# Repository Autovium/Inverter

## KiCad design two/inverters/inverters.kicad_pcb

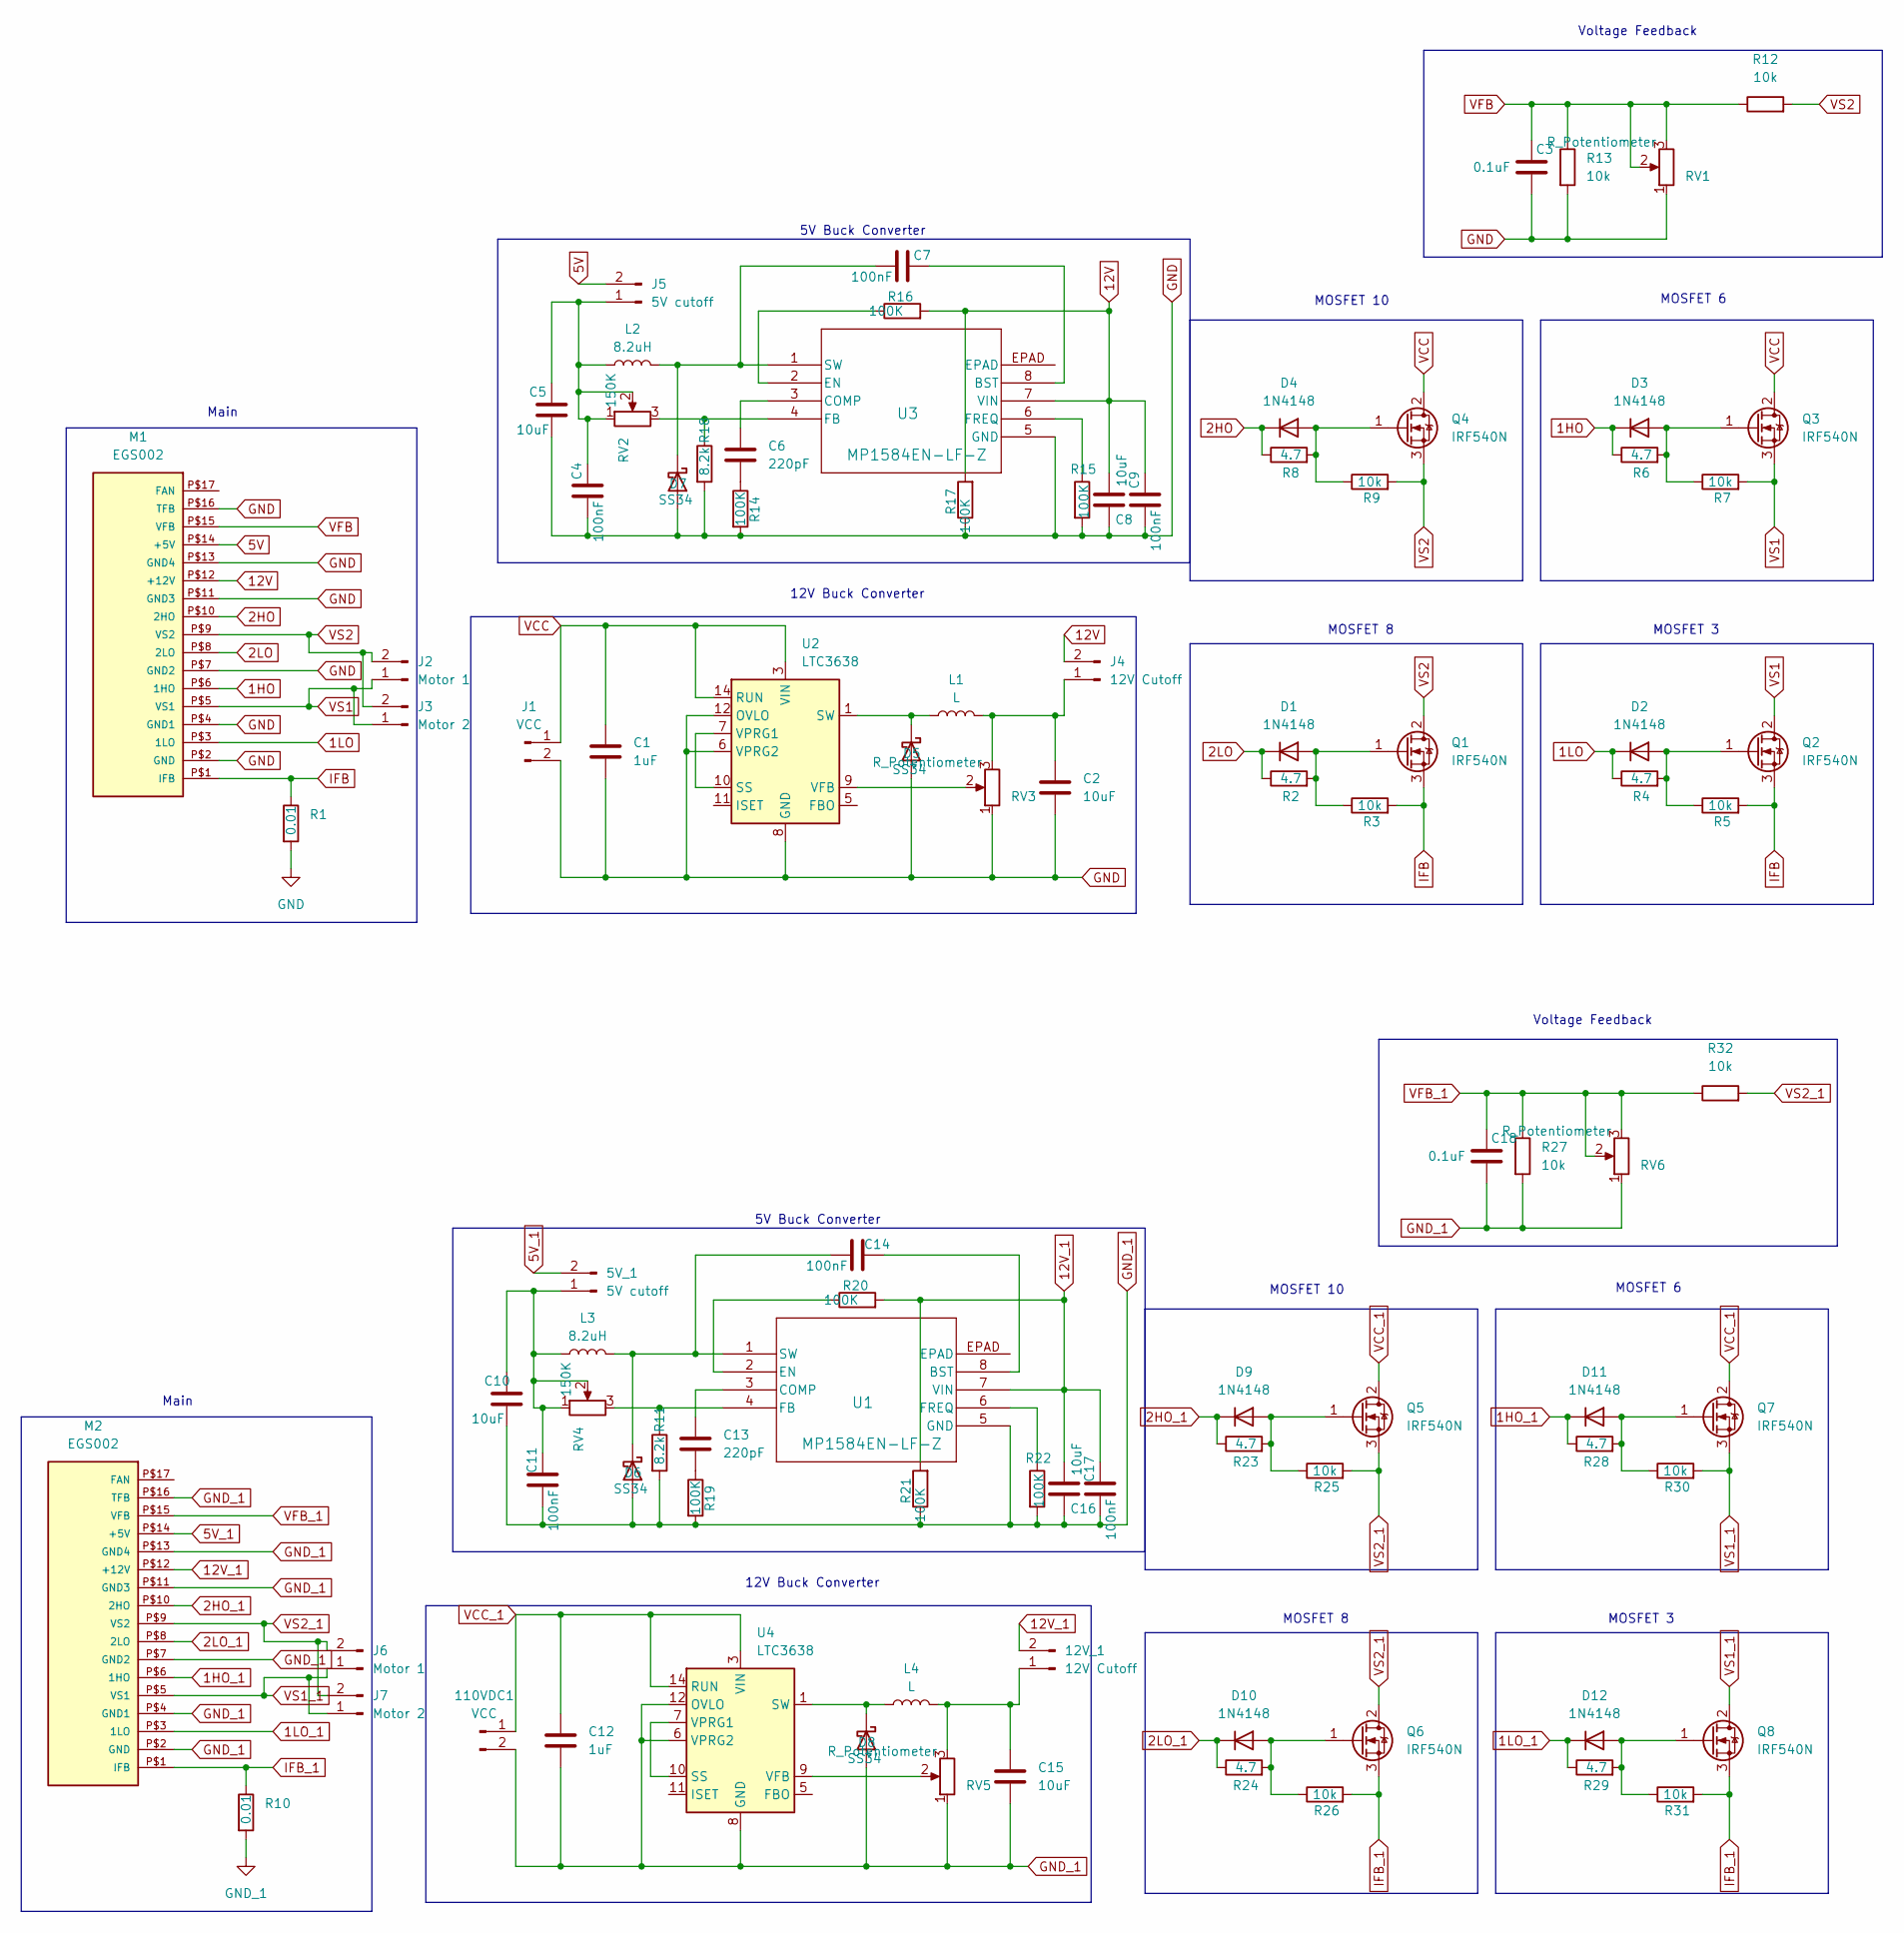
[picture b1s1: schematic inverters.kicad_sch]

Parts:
5V_1: 5V cutoff; SolderJumper-2_P1.3mm_Open_Pad1.0x1.5mm
12V_1: 12V Cutoff; SolderJumper-2_P1.3mm_Open_Pad1.0x1.5mm
110VDC1: VCC; PinHeader_1x02_P2.54mm_Vertical
C1: 1uF; C_Disc_D3.0mm_W1.6mm_P2.50mm
C2: 10uF; C_Disc_D3.0mm_W1.6mm_P2.50mm
C3, C18: 0.1uF; C_Disc_D3.0mm_W1.6mm_P2.50mm
C4, C7, C9, C11, C14, C17: 100nF; C_0201_0603Metric_Pad0.64x0.40mm_HandSolder
C5, C8, C10, C16: 10uF; C_1206_3216Metric_Pad1.33x1.80mm_HandSolder
C6, C13: 220pF; C_0201_0603Metric_Pad0.64x0.40mm_HandSolder
C12: 1uF; CP_Radial_D4.0mm_P2.00mm
C15: 10uF; CP_Radial_D4.0mm_P2.00mm
D1, D2, D3, D4, D9, D10, D11, D12: 1N4148; Nexperia_CFP3_SOD-123W
D5, D6, D7, D8: SS34; D_SMA_Handsoldering
J1: VCC; PinHeader_1x02_P2.54mm_Vertical
J2, J6: Motor 1; PinHeader_1x02_P2.54mm_Vertical
J3, J7: Motor 2; PinHeader_1x02_P2.54mm_Vertical
J4: 12V Cutoff; SolderJumper-2_P1.3mm_Open_Pad1.0x1.5mm
J5: 5V cutoff; PinHeader_1x02_P1.00mm_Vertical_SMD_Pin1Left
L1, L4: L; L_Radial_D6.0mm_P4.00mm
L2, L3: 8.2uH; L_Bourns_SRP6060FA
M1, M2: EGS002
Q1, Q2, Q3, Q4, Q5, Q6, Q7, Q8: IRF540N; TO-220-3_Vertical
R1: 0.01; R_Axial_DIN0204_L3.6mm_D1.6mm_P5.08mm_Horizontal
R2, R4, R6, R8: 4.7; R_0805_2012Metric_Pad1.20x1.40mm_HandSolder
R3, R5, R7, R9, R12, R13: 10k; R_0805_2012Metric_Pad1.20x1.40mm_HandSolder
R10: 0.01; R_Axial_DIN0207_L6.3mm_D2.5mm_P7.62mm_Horizontal
R11, R18: 8.2k; R_0201_0603Metric_Pad0.64x0.40mm_HandSolder
R14, R15, R16, R17, R19, R20, R21, R22: 100K; R_0201_0603Metric_Pad0.64x0.40mm_HandSolder
R23, R24, R28, R29: 4.7; R_Axial_DIN0207_L6.3mm_D2.5mm_P7.62mm_Horizontal
R25, R26, R27, R30, R31, R32: 10k; R_Axial_DIN0207_L6.3mm_D2.5mm_P7.62mm_Horizontal
RV1, RV3, RV5, RV6: R_Potentiometer; Potentiometer_Bourns_3266Y_Vertical
RV2, RV4: 150K; Potentiometer_Bourns_TC33X_Vertical
U1, U3: MP1584EN-LF-Z; SOIC8E_MPS
U2, U4: LTC3638; Linear_MSOP-12-16-1EP_3x4mm_P0.5mm

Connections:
1HO: D3.1 (K), M1.P$6 (1HO), R6.1
1HO_1: D11.1 (K), M2.P$6 (1HO), R28.1
1LO: D2.1 (K), M1.P$3 (1LO), R4.1
1LO_1: D12.1 (K), M2.P$3 (1LO), R29.1
2HO: D4.1 (K), M1.P$10 (2HO), R8.1
2HO_1: D9.1 (K), M2.P$10 (2HO), R23.1
2LO: D1.1 (K), M1.P$8 (2LO), R2.1
2LO_1: D10.1 (K), M2.P$8 (2LO), R24.1
5V: J5.2, M1.P$14 (+5V)
5V_1: 5V_1.2, M2.P$14 (+5V)
12V: C8.1, C9.2, J4.2, M1.P$12 (+12V), R16.2, R17.2, U3.7 (VIN)
12V_1: 12V_1.2, C16.1, C17.2, M2.P$12 (+12V), R20.2, R21.2, U1.7 (VIN)
GND: C1.2, C2.2, C3.2, C4.1, C5.2, C8.2, C9.1, D5.2 (A), D7.2 (A), J1.2, M1.P$2 (GND), M1.P$4 (GND1), M1.P$7 (GND2), M1.P$11 (GND3), M1.P$13 (GND4), M1.P$16 (TFB), R1.2, R13.2, R14.2, R15.2, R17.1, R18.2, RV1.1, RV3.1, U2.6 (VPRG2), U2.8 (GND), U2.12 (OVLO), U2.16 (GND), U2.17 (GND), U3.5 (GND)
GND_1: 110VDC1.2, C10.2, C11.1, C12.2, C15.2, C16.2, C17.1, C18.2, D6.2 (A), D8.2 (A), M2.P$2 (GND), M2.P$4 (GND1), M2.P$7 (GND2), M2.P$11 (GND3), M2.P$13 (GND4), M2.P$16 (TFB), R10.2, R11.2, R19.2, R21.1, R22.2, R27.2, RV5.1, RV6.1, U1.5 (GND), U4.6 (VPRG2), U4.8 (GND), U4.12 (OVLO), U4.16 (GND), U4.17 (GND)
IFB: M1.P$1 (IFB), Q1.3 (S), Q2.3 (S), R1.1, R3.2, R5.2
IFB_1: M2.P$1 (IFB), Q6.3 (S), Q8.3 (S), R10.1, R26.2, R31.2
unnamed: 5V_1.1, C10.1, C11.2, L3.1, RV4.1, RV4.2
unnamed: 12V_1.1, C15.1, L4.2, RV5.3
unnamed: C6.2, R14.1
unnamed: C13.2, R19.1
unnamed: D1.2 (A), Q1.1 (G), R2.2, R3.1
unnamed: D2.2 (A), Q2.1 (G), R4.2, R5.1
unnamed: D3.2 (A), Q3.1 (G), R6.2, R7.1
unnamed: D4.2 (A), Q4.1 (G), R8.2, R9.1
unnamed: D5.1 (K), L1.1, U2.1 (SW)
unnamed: C14.1, D6.1 (K), L3.2, U1.1 (SW)
unnamed: C7.1, D7.1 (K), L2.2, U3.1 (SW)
unnamed: D8.1 (K), L4.1, U4.1 (SW)
unnamed: D9.2 (A), Q5.1 (G), R23.2, R25.1
unnamed: D10.2 (A), Q6.1 (G), R24.2, R26.1
unnamed: D11.2 (A), Q7.1 (G), R28.2, R30.1
unnamed: D12.2 (A), Q8.1 (G), R29.2, R31.1
unnamed: C2.1, J4.1, L1.2, RV3.3
unnamed: C4.2, C5.1, J5.1, L2.1, RV2.1, RV2.2
unnamed: C14.2, U1.8 (BST)
unnamed: C13.1, U1.3 (COMP)
unnamed: R20.1, U1.2 (EN)
unnamed: R11.1, RV4.3, U1.4 (FB)
unnamed: R22.1, U1.6 (FREQ)
unnamed: U2.7 (VPRG1), U2.10 (SS)
unnamed: RV3.2, U2.9 (VFB)
unnamed: C7.2, U3.8 (BST)
unnamed: C6.1, U3.3 (COMP)
unnamed: R16.1, U3.2 (EN)
unnamed: R18.1, RV2.3, U3.4 (FB)
unnamed: R15.1, U3.6 (FREQ)
unnamed: U4.7 (VPRG1), U4.10 (SS)
unnamed: RV5.2, U4.9 (VFB)
VCC: C1.1, J1.1, Q3.2 (D), Q4.2 (D), U2.3 (VIN), U2.14 (RUN)
VCC_1: 110VDC1.1, C12.1, Q5.2 (D), Q7.2 (D), U4.3 (VIN), U4.14 (RUN)
VFB: C3.1, M1.P$15 (VFB), R12.1, R13.1, RV1.2, RV1.3
VFB_1: C18.1, M2.P$15 (VFB), R27.1, R32.1, RV6.2, RV6.3
VS1: J2.1, J3.1, M1.P$5 (VS1), Q2.2 (D), Q3.3 (S), R7.2
VS1_1: J6.1, J7.1, M2.P$5 (VS1), Q7.3 (S), Q8.2 (D), R30.2
VS2: J2.2, J3.2, M1.P$9 (VS2), Q1.2 (D), Q4.3 (S), R9.2, R12.2
VS2_1: J6.2, J7.2, M2.P$9 (VS2), Q5.3 (S), Q6.2 (D), R25.2, R32.2

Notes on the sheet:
MOSFET 10
12V Buck Converter
Main
MOSFET 8
Voltage Feedback
5V Buck Converter
MOSFET 3
MOSFET 6

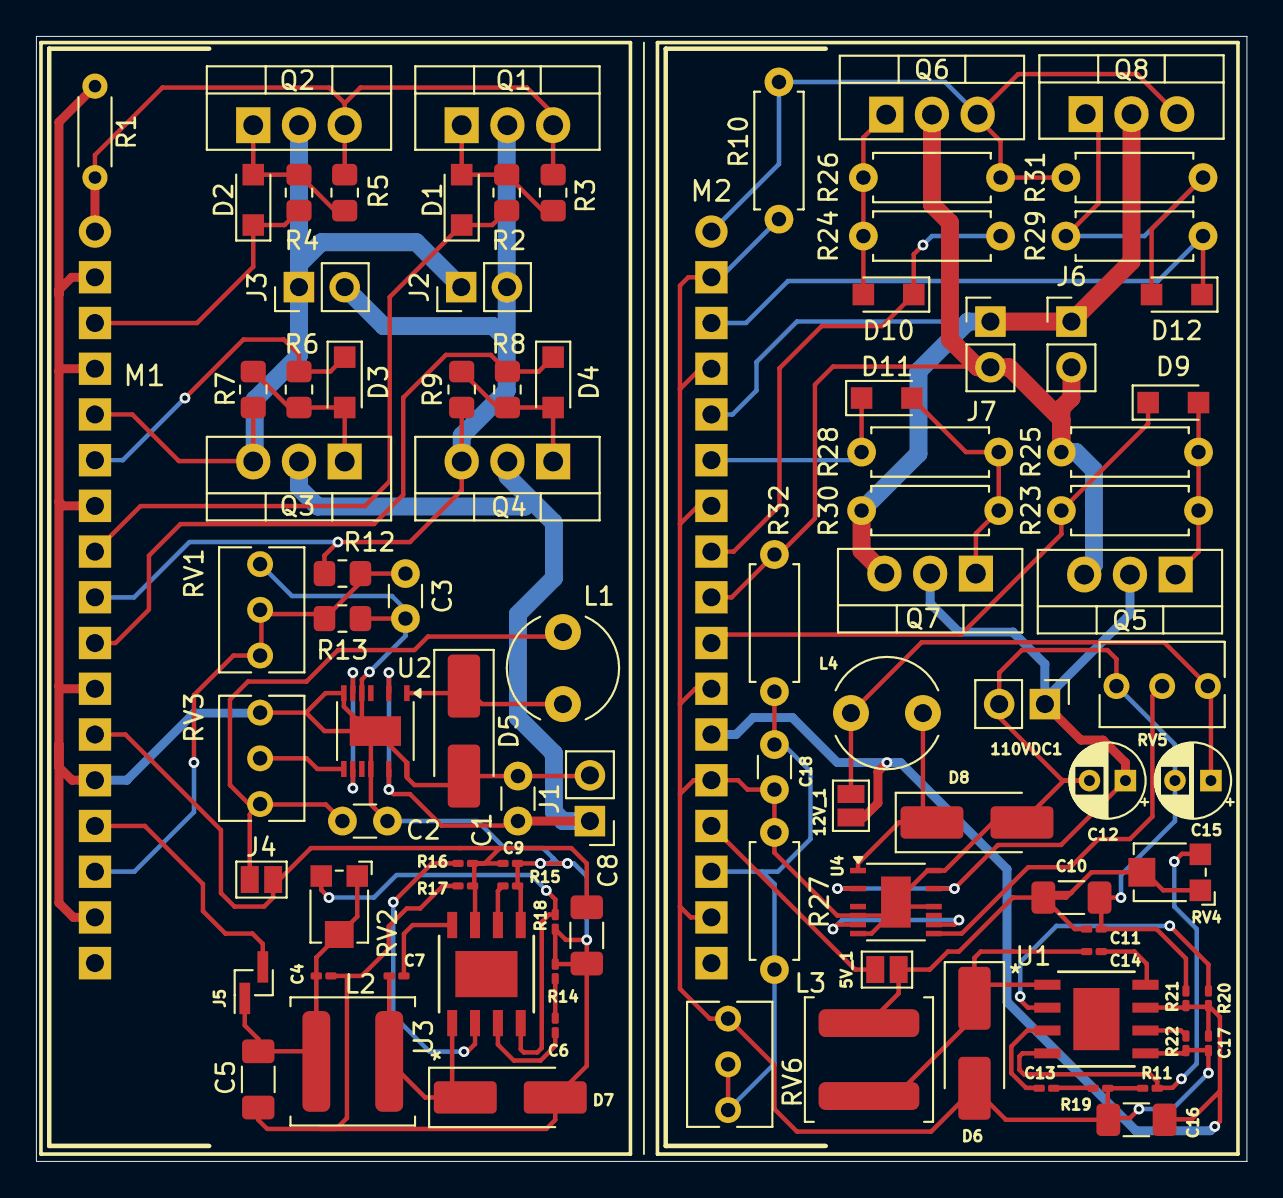
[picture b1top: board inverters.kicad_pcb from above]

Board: 2 copper layers, 67.2 x 62.5 mm, 96 parts (0 on the bottom side), 56 nets.

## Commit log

2025-04-09 First version
2025-04-09 second version
2025-04-09 version with 2 inverters
